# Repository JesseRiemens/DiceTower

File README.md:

# DiceTower - A 3D-Printed Electronic Dice Tower

View this project on [CADLAB.io](https://cadlab.io/project/27312).

## System Architecture Diagram

## Bill of Materials

| Item                                   | Quantity | Price (Estimated) | Link                                  |
| -------------------------------------- | -------- | ----------------- | ------------------------------------- |
| ESP32 Feather Huzzah32                 | 1        | $20.22            | [DigiKey-ESP32]                       |
| LCD 20x4                               | 1        | $20.26            | [DigiKey-LCD]                         |
| PCB                                    | 1        | $5.00             | [PCBWay]; [JLCPCB]                    |
| 3D-Printed Parts                       | 1        | $10.00            |
| Incremental Encoder                    | 1        | $1.00             | [TinyTronics-Encoder]                 |
| Encoder Knob                           | 1        | $1.00             | [TinyTronics-Encoder-Knob]            |
| Dice (d4, d6, d8, d10, d12, d20, d100) | 1        | $10.00            |
| Switches                               | 7        | $9.99             |
| Dice keycaps printed                   | 7        | $1.00             |
| Boost Converter                        | 1        | $2.00             | [TinyTronics-Boost-Converter]         |
| Battery                                | 1        | $5.00             | [TinyTronics-Battery]                 |

[DigiKey-ESP32]: https://www.digikey.nl/en/products/detail/adafruit-industries-llc/3619/8119806
[DigiKey-LCD]: https://www.digikey.nl/en/products/detail/newhaven-display-intl/NHD-0420AZ-FSW-GBW-33V3/2773596
[PCBWay]: https://www.pcbway.com
[JLCPCB]: https://jlcpcb.com
[TinyTronics-Encoder]: https://www.tinytronics.nl/shop/nl/schakelaars/manuele-schakelaars/rotary-encoders/rotary-encoder-module
[TinyTronics-Encoder-Knob]: https://www.tinytronics.nl/shop/nl/componenten/knoppen,-doppen-en-kapjes/potmeter-knop-zwart
[TinyTronics-Boost-Converter]: https://www.tinytronics.nl/shop/en/power/voltage-converters/boost-(step-up)-converters/mini-dc-dc-3.3v-step-up-boost-converter-400ma
[TinyTronics-Battery]: https://www.tinytronics.nl/shop/en/power/batteries/li-po/li-po-battery-3.7v-1250mah-jst-ph-lp554050

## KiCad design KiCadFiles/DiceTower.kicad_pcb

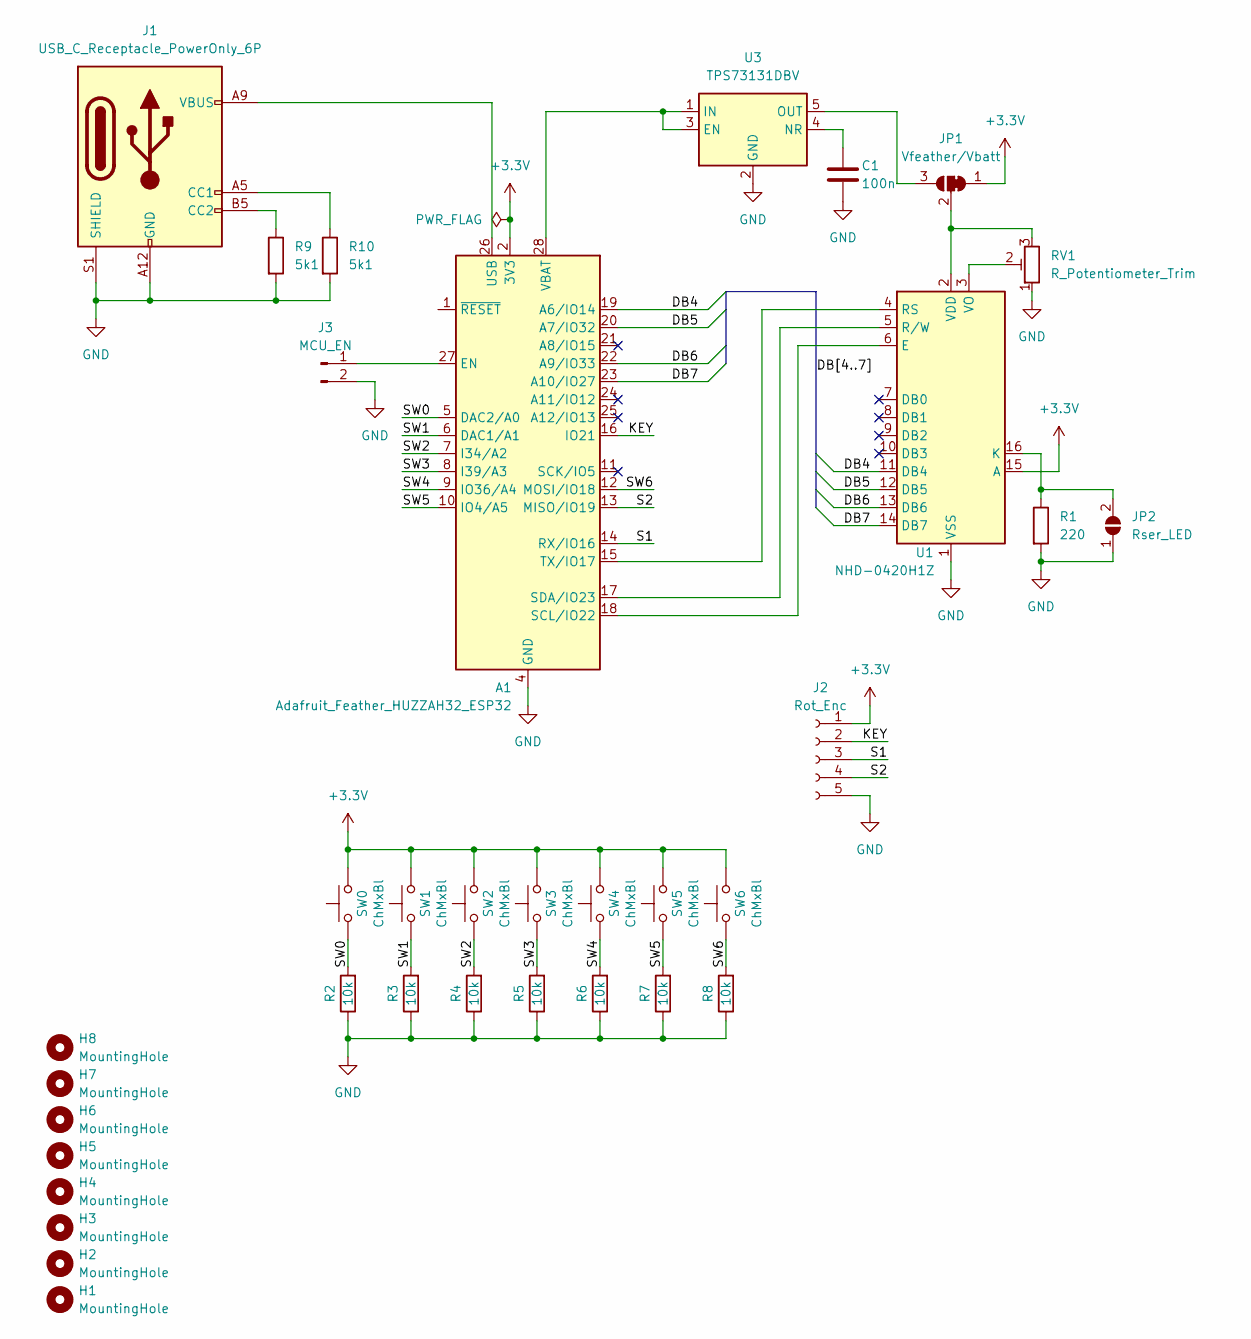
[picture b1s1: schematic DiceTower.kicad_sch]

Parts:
A1: Adafruit_Feather_HUZZAH32_ESP32; Adafruit_Feather
C1: 100n; C_0603_1608Metric
H1, H2, H3, H4, H5, H6, H7, H8: MountingHole; MountingHole_3.2mm_M3_ISO14580
J1: USB_C_Receptacle_PowerOnly_6P; USB_C_Receptacle_GCT_USB4125-xx-x-0190_6P_TopMnt_Horizontal
J2: Rot_Enc; PinSocket_1x05_P2.54mm_Vertical
J3: MCU_EN; PinHeader_1x02_P2.54mm_Vertical
JP1: Vfeather/Vbatt; SolderJumper-3_P1.3mm_Bridged12_RoundedPad1.0x1.5mm_NumberL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
JP2: Rser_LED; SolderJumper-2_P1.3mm_Open_RoundedPad1.0x1.5mm
R1: 220; R_0603_1608Metric_Pad0.98x0.95mm_HandSolder
R2, R3, R4, R5, R6, R7, R8: 10k; R_0603_1608Metric_Pad0.98x0.95mm_HandSolder
R9, R10: 5k1; R_0603_1608Metric_Pad0.98x0.95mm_HandSolder
RV1: R_Potentiometer_Trim; Potentiometer_Bourns_3266W_Vertical
SW0, SW1, SW2, SW3, SW4, SW5, SW6: ChMxBl; SW_Cherry_MX_1.00u_PCB
U1: NHD-0420H1Z; PinHeader_1x16_P2.54mm_Vertical
U3: TPS73131DBV; SOT-23-5

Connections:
+3.3V: A1.2 (3V3), J2.1, JP1.1 (A), SW0.2, SW1.2, SW2.2, SW3.2, SW4.2, SW5.2, SW6.2, U1.15 (A)
/DB4: A1.19 (A6/IO14), U1.11 (DB4)
/DB5: A1.20 (A7/IO32), U1.12 (DB5)
/DB6: A1.22 (A9/IO33), U1.13 (DB6)
/DB7: A1.23 (A10/IO27), U1.14 (DB7)
/KEY: A1.16 (IO21), J2.2
/S1: A1.14 (RX/IO16), J2.3
/S2: A1.13 (MISO/IO19), J2.4
/SW0: A1.5 (DAC2/A0), R2.2, SW0.1
/SW1: A1.6 (DAC1/A1), R3.2, SW1.1
/SW2: A1.7 (I34/A2), R4.2, SW2.1
/SW3: A1.8 (I39/A3), R5.2, SW3.1
/SW4: A1.9 (IO36/A4), R6.2, SW4.1
/SW5: A1.10 (IO4/A5), R7.2, SW5.1
/SW6: A1.12 (MOSI/IO18), R8.2, SW6.1
GND: A1.4 (GND), C1.2, J1.A12 (GND), J1.B12 (GND), J1.S1 (SHIELD), J2.5, J3.2, JP2.1 (A), R1.2, R2.1, R3.1, R4.1, R5.1, R6.1, R7.1, R8.1, R9.2, R10.2, RV1.1, U1.1 (VSS), U3.2 (GND)
unnamed: A1.27 (EN), J3.1
unnamed: A1.18 (SCL/IO22), U1.6 (E)
unnamed: A1.17 (SDA/IO23), U1.5 (R/W)
unnamed: A1.15 (TX/IO17), U1.4 (RS)
unnamed: A1.26 (USB), J1.A9 (VBUS), J1.B9 (VBUS)
unnamed: A1.28 (VBAT), U3.1 (IN), U3.3 (EN)
unnamed: J1.A5 (CC1), R10.1
unnamed: J1.B5 (CC2), R9.1
unnamed: JP1.3 (B), U3.5 (OUT)
unnamed: JP1.2 (C), RV1.3, U1.2 (VDD)
unnamed: JP2.2 (B), R1.1, U1.16 (K)
unnamed: RV1.2, U1.3 (VO)
unnamed: C1.1, U3.4 (NR)

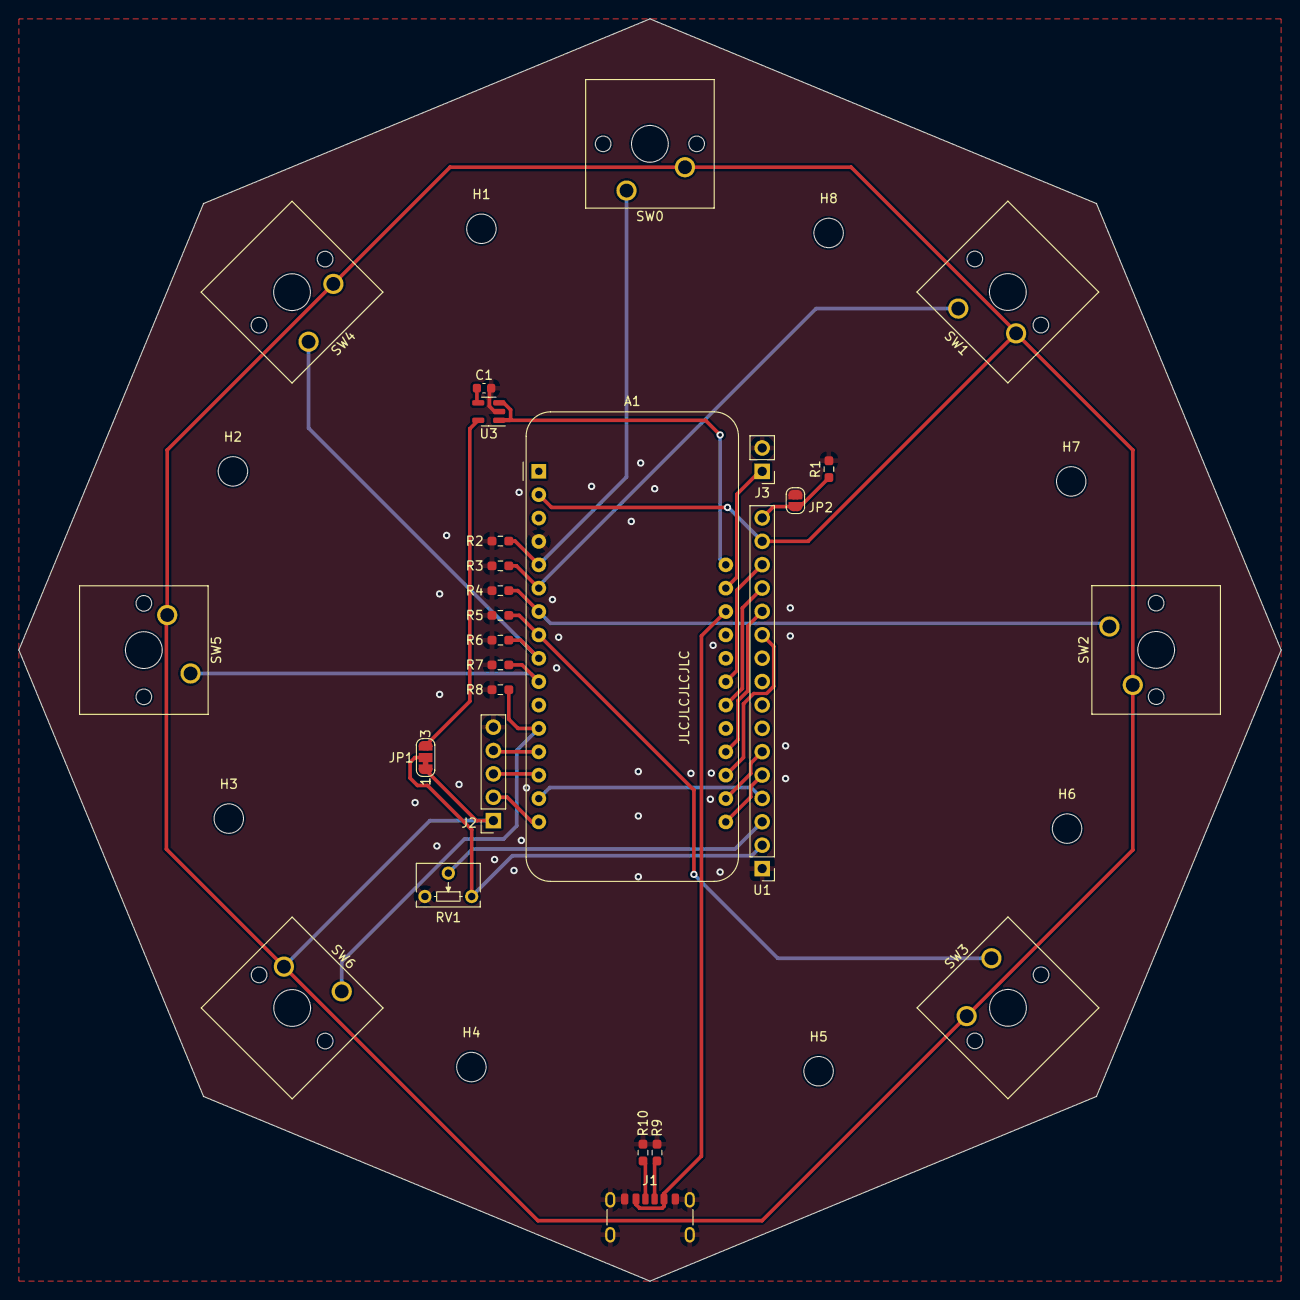
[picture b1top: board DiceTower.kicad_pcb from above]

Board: 2 copper layers, 137.2 x 137.2 mm, 35 parts (0 on the bottom side), 29 nets.

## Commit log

2023-09-09 Backlink to CADLAB.io has been added.
2023-09-09 Schematic draft
2023-09-09 Add system diagram
2023-09-09 Add BOM
2023-09-09 Add BOM, updated schematics
2023-09-09 Update BOM
2023-09-09 Update background color
2023-09-09 PNG to keep background
2023-09-09 Change architecture
2023-09-10 Change display to 3.3V
2023-09-10 Add PCB
2023-09-15 Add zepyhr project
2023-09-15 Local build
2023-09-15 Change build folder
2023-09-15 Shortcut build
2023-09-15 Cleanup
2023-09-15 Add picocom monitor
2023-09-15 Add three threads
2023-09-16 Add input
2023-09-16 Octagon
2023-11-07 Moved board to key circle
2023-11-08 Added usb-c connector
2023-11-08 Finish PCB
2023-11-09 Try to add gerbers pipeline
2023-11-10 Change resistor location
2023-11-11 Add mounting holes
2023-11-13 Edit outline edgecuts
2023-11-13 Ignore production files
2023-11-13 Collect all the chaos nachos!
2023-12-03 Update build.yml and add new files for tests
2023-12-03 Fix board platform
2023-12-04 Add sample driver for this display
2023-12-27 Remove unused esp32 overlay
2023-12-27 add dxf to gitignore
